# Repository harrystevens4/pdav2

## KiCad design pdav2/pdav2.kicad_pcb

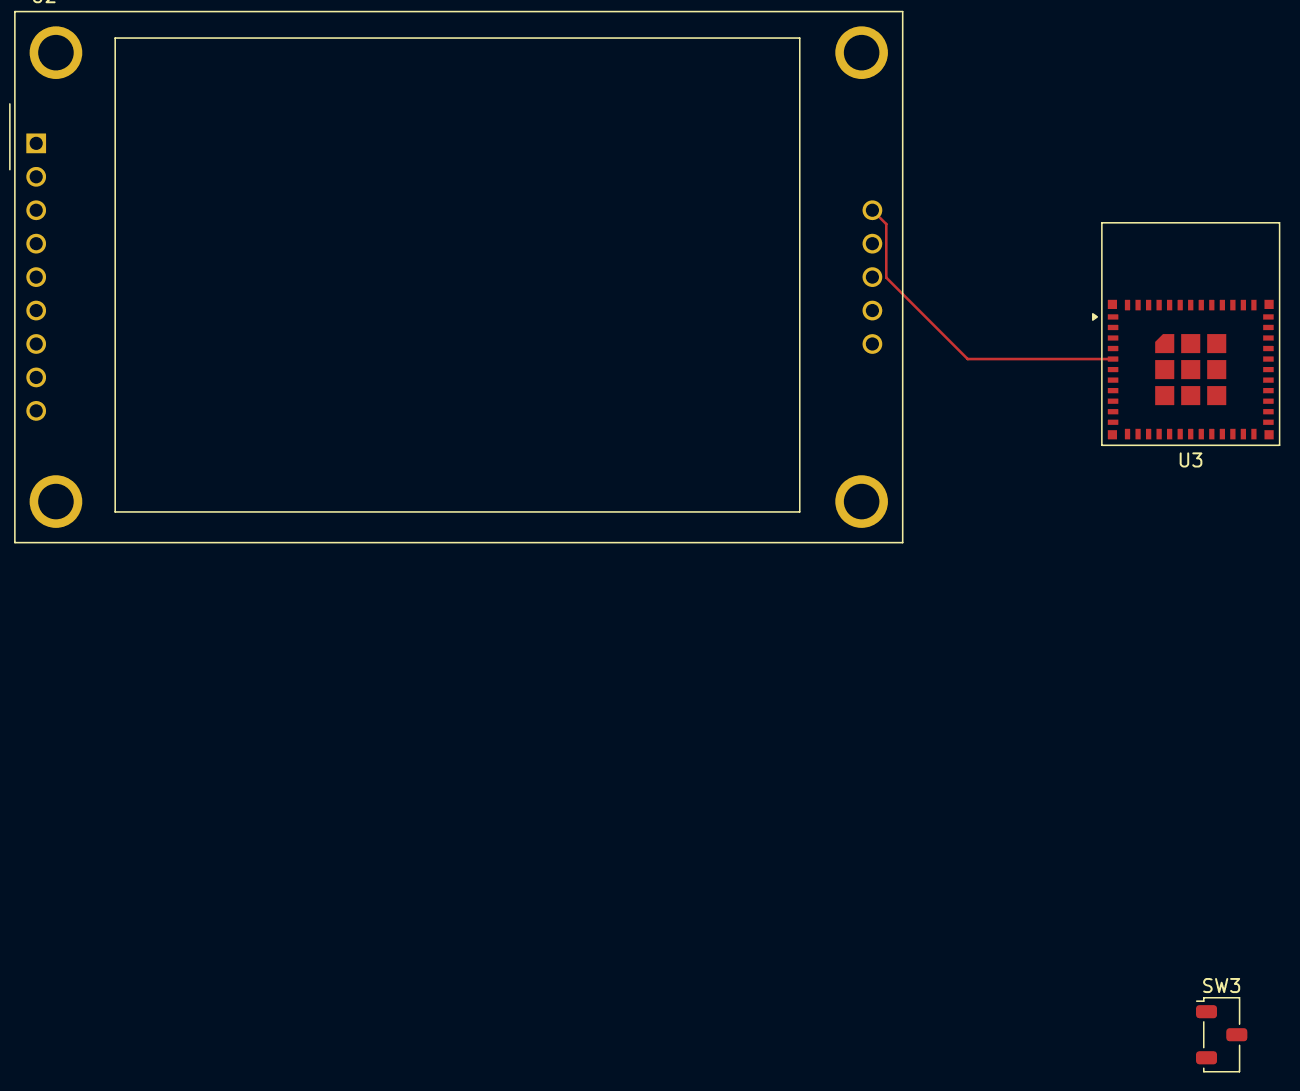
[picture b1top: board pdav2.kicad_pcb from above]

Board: 2 copper layers, 3 parts (0 on the bottom side), 9 nets.

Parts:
SW3: SW_Nidec_CAS-120A1; Nidec_Copal_CAS-120A
U2: CR2013-MI2120
U3: ESP32-C6-MINI-1

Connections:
unnamed: SW3.2 (B), U3.1 (GND), U3.2 (GND), U3.11 (GND), U3.14 (GND), U3.36 (GND), U3.37 (GND), U3.38 (GND), U3.39 (GND), U3.40 (GND), U3.41 (GND), U3.42 (GND), U3.43 (GND), U3.44 (GND), U3.45 (GND), U3.46 (GND), U3.47 (GND), U3.48 (GND), U3.49 (GND), U3.50 (GND), U3.51 (GND), U3.52 (GND), U3.53 (GND)
unnamed: U2.5 (D/~C), U3.6 (IO3)
unnamed: U2.8 (LED), U3.22 (IO8)
unnamed: U2.9 (MISO), U2.12 (SD_MISO), U3.15 (IO6)
unnamed: U2.6 (MOSI), U2.11 (SD_MOSI), U3.10 (IO5)
unnamed: U2.4 (RESET), U3.23 (IO9)
unnamed: U2.7 (SCK), U2.13 (SD_SCK), U3.16 (IO7)
unnamed: U2.10 (SD_CS), U3.5 (IO2)
unnamed: U2.3 (~CS), U3.9 (IO4)

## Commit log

2026-02-06 initial commit with working rotary encoder class
2026-02-06 rotated screen
2026-02-07 added sd card tests
2026-02-08 found working sd card code
2026-02-08 added main menu
2026-02-08 improved accuracy
2026-02-08 added button support
2026-02-08 added button press detection in menus
2026-02-18 created kicad project for PCB design
